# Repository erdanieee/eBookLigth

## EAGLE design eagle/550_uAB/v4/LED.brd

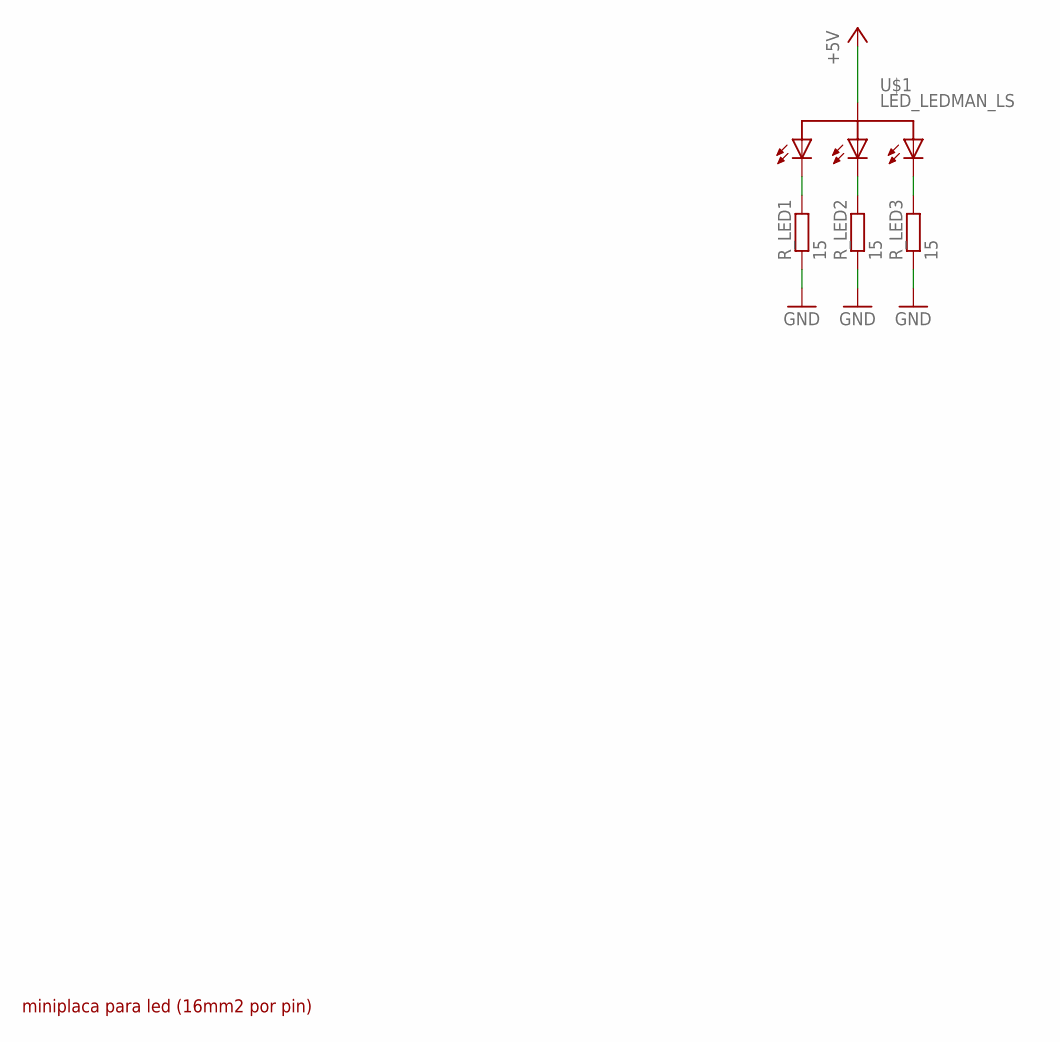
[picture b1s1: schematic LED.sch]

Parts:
R_LED1, R_LED2, R_LED3: 15; R1206
U$1: LED_LEDMAN_LS

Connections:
+5V: U$1.2 (ANODO)
GND: R_LED1.1, R_LED2.1, R_LED3.1
unnamed: R_LED1.2, U$1.1 (C1)
unnamed: R_LED2.2, U$1.3 (C2)
unnamed: R_LED3.2, U$1.4 (C3)

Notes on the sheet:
miniplaca para led (16mm2 por pin)

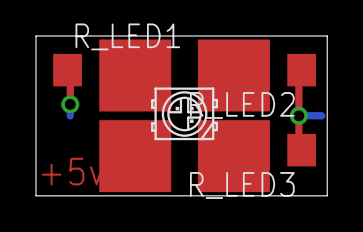
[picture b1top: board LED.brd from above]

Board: 2 copper layers, 16.2 x 8.9 mm, 4 parts (0 on the bottom side), 4 nets.

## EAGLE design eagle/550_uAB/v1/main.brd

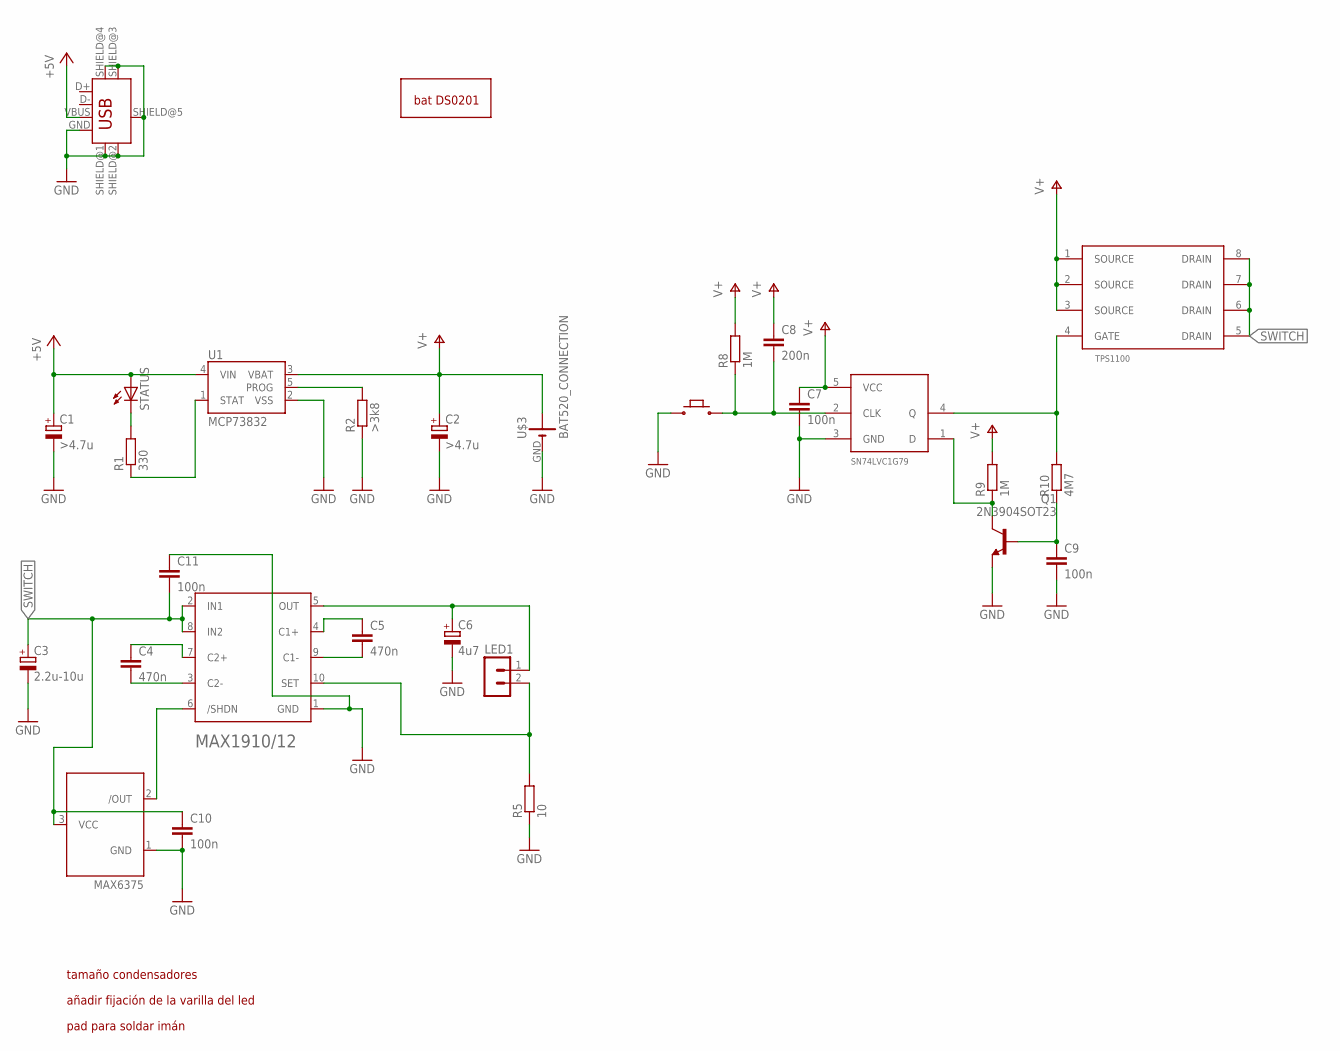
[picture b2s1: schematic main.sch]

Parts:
C1, C2: >4.7u; SMC_B
C3: 2.2u-10u; SMC_B
C4, C5: 470n; C1206
C6: 4u7; SMC_B
C7, C9, C10, C11: 100n; C1206
C8: 200n; C1206
LED1: MA02-1; MA02-1W
Q1: 2N3904SOT23; SOT23
R1: 330; R1206
R2: >3k8; R1206
R5: 10; R1206
R8, R9: 1M; R0805
R10: 4M7; R1206
STATUS: LEDCHIPLED_1206; CHIPLED_1206
U1: MCP73832; SOT23-5
U$1: MAX1910/12; UMAX/USOP_10L
U$2: MAX6375; SC70-3-W
U$3: BAT520_CONNECTION; BAT520_CONN_SMD
U$4: BAT_DS0201_PACKAGE; BAT_DS0201
U$5: MICROUSB_B; USB-MICROB
U$6: MICROBUTTON_0072; MICROBUTTON
U$7: SN74LVC1G79; SOT23-5
U$8: TPS1100; SO08

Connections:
+5V: C1.+, STATUS.A, U1.4 (VIN), U$5.VBUS
GND: C1.-, C2.-, C3.-, C6.-, C7.2, C9.2, C10.2, C11.1, Q1.2 (E), R2.1, R5.1, U1.2 (VSS), U$1.1 (GND), U$2.1 (GND), U$3.GND (-), U$5.GND, U$5.SHIELD@1 (SHIELD), U$5.SHIELD@2 (SHIELD), U$5.SHIELD@3 (SHIELD), U$5.SHIELD@4 (SHIELD), U$5.SHIELD@5 (SHIELD), U$6.P$2, U$7.3 (GND)
unnamed: Q1.3 (C), R9.1, U$7.1 (D)
unnamed: R1.2, STATUS.C
unnamed: R2.2, U1.5 (PROG)
unnamed: R1.1, U1.1 (STAT)
unnamed: C4.2, U$1.3 (C2-)
unnamed: C4.1, U$1.7 (C2+)
unnamed: C5.2, U$1.9 (C1-)
unnamed: C5.1, U$1.4 (C1+)
unnamed: LED1.2, R5.2, U$1.10 (SET)
unnamed: C6.+, LED1.1, U$1.5 (OUT)
unnamed: U$1.6 (/SHDN), U$2.2 (/OUT)
unnamed: C8.2, R8.1, U$6.P$1, U$7.2 (CLK)
unnamed: C9.1, Q1.1 (B), R10.1
unnamed: R10.2, U$7.4 (Q), U$8.4 (GATE)
SWITCH: C3.+, C10.1, C11.2, U$1.2 (IN1), U$1.8 (IN2), U$2.3 (VCC), U$8.5 (DRAIN), U$8.6 (DRAIN), U$8.7 (DRAIN), U$8.8 (DRAIN)
V+: C2.+, C7.1, C8.1, R8.2, R9.2, U1.3 (VBAT), U$3.VCC (+), U$7.5 (VCC), U$8.1 (SOURCE), U$8.2 (SOURCE), U$8.3 (SOURCE)

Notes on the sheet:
tamaño condensadores
añadir fijación de la varilla del led
pad para soldar imán

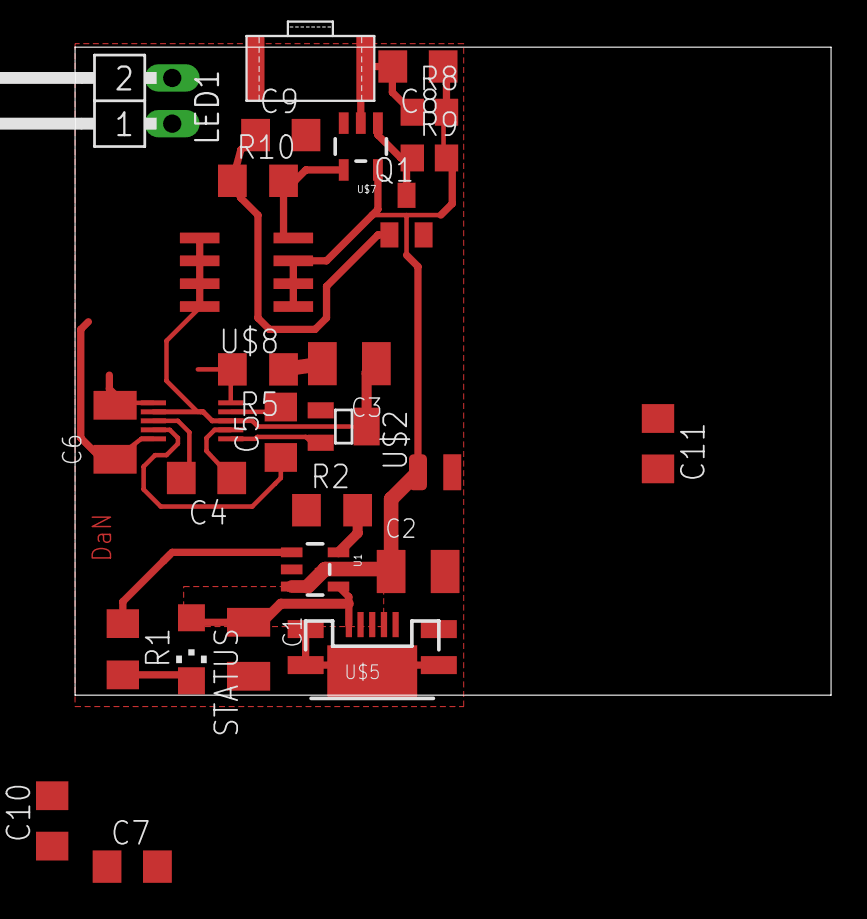
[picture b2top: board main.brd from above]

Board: 2 copper layers, 42.0 x 36.0 mm, 29 parts (0 on the bottom side), 18 nets.

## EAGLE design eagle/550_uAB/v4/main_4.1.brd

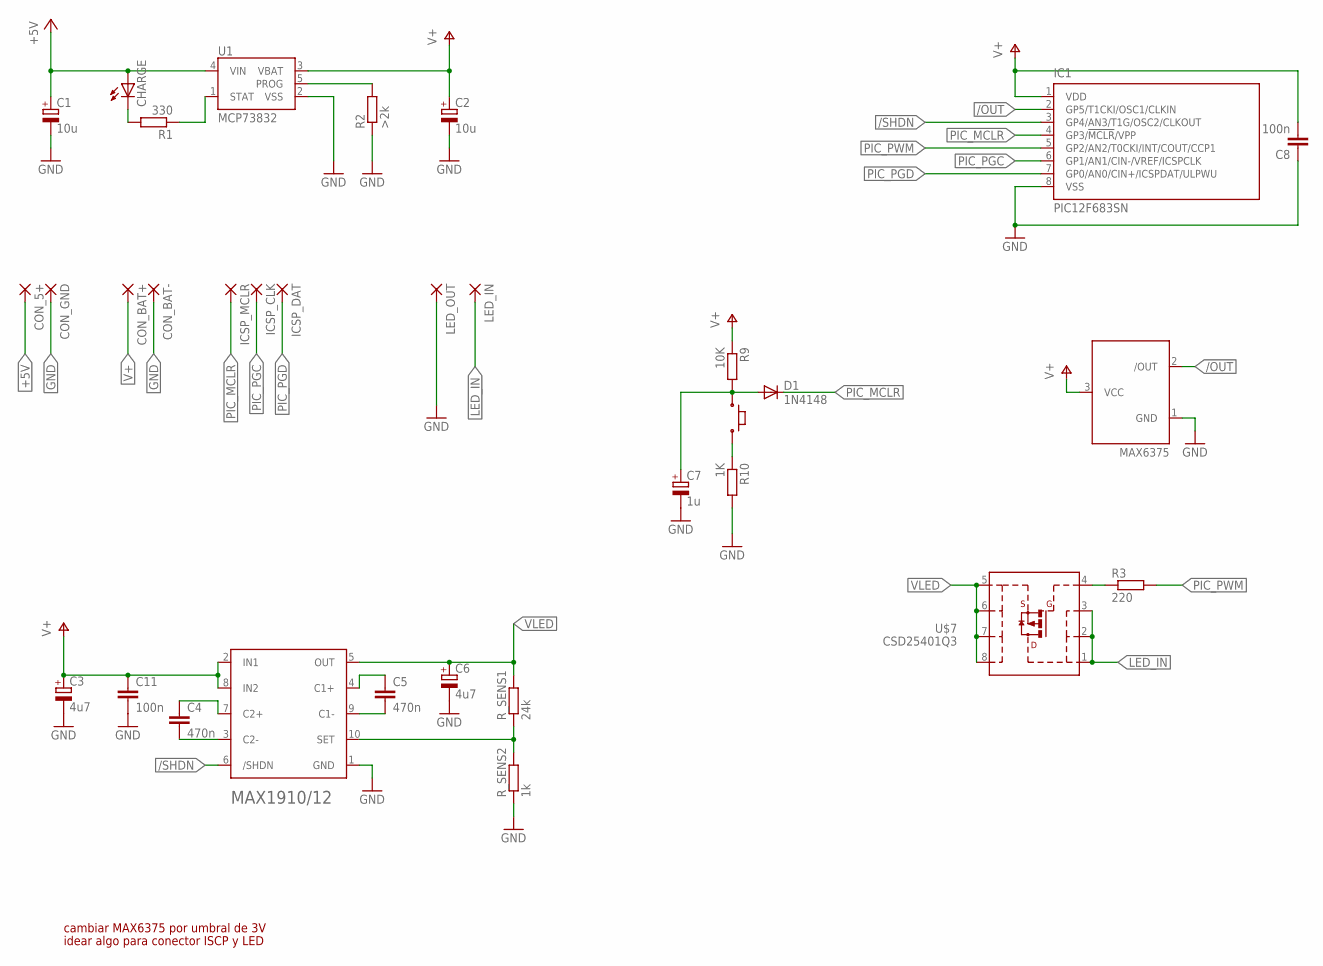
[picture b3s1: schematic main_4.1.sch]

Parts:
C1, C2: 10u; SMC_A
C3, C6: 4u7; SMC_A
C4, C5: 470n; C1206
C7: 1u; SMC_A
C8, C11: 100n; C1206
CHARGE: LEDCHIPLED_1206; CHIPLED_1206
CON_5+: SMD5; SMD2,54-5,08
CON_BAT+: SMD5; SMD2,54-5,08
CON_BAT-: SMD5; SMD2,54-5,08
CON_GND: SMD5; SMD2,54-5,08
D1: 1N4148; SOD80
IC1: PIC12F683SN; SO-08
ICSP_CLK: SMD5; SMD2,54-5,08
ICSP_DAT: SMD5; SMD2,54-5,08
ICSP_MCLR: SMD5; SMD2,54-5,08
LED_IN: SMD5; SMD2,54-5,08
LED_OUT: SMD5; SMD2,54-5,08
R1: 330; R1206
R2: >2k; R1206
R3: 220; R1206
R9: 10K; R1206
R10: 1K; R1206
R_SENS1: 24k; R1206
R_SENS2: 1k; R1206
U1: MCP73832; SOT23-5
U$1: MAX1910/12; UMAX/USOP_10L
U$2: MAX6375; SC70-3-W
U$6: MICROBUTTONE-MERCHAN; MICROBUTTON_2
U$7: CSD25401Q3; SON3X3

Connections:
+5V: C1.+, CHARGE.A, CON_5+.1, U1.4 (VIN)
/OUT: IC1.2 (GP5/T1CKI/OSC1/CLKIN), U$2.2 (/OUT)
/SHDN: IC1.3 (GP4/AN3/T1G/OSC2/CLKOUT), U$1.6 (/SHDN)
BUT: C7.+, D1.1 (A), R9.2, U$6.P$1
GND: C1.-, C2.-, C3.-, C6.-, C7.-, C8.1, C11.2, CON_BAT-.1, CON_GND.1, IC1.8 (VSS), LED_OUT.1, R2.1, R10.2, R_SENS2.1, U1.2 (VSS), U$1.1 (GND), U$2.1 (GND)
LED_IN: LED_IN.1, U$7.1, U$7.2, U$7.3
unnamed: R_SENS1.1, R_SENS2.2, U$1.10 (SET)
unnamed: R2.2, U1.5 (PROG)
unnamed: R1.1, U1.1 (STAT)
unnamed: C4.2, U$1.3 (C2-)
unnamed: C4.1, U$1.7 (C2+)
unnamed: C5.2, U$1.9 (C1-)
unnamed: C5.1, U$1.4 (C1+)
unnamed: R10.1, U$6.P$2
unnamed: R3.1, U$7.4
unnamed: CHARGE.C, R1.2
PIC_MCLR: D1.2 (C), IC1.4 (GP3/!MCLR!/VPP), ICSP_MCLR.1
PIC_PGC: IC1.6 (GP1/AN1/CIN-/VREF/ICSPCLK), ICSP_CLK.1
PIC_PGD: IC1.7 (GP0/AN0/CIN+/ICSPDAT/ULPWU), ICSP_DAT.1
PIC_PWM: IC1.5 (GP2/AN2/T0CKI/INT/COUT/CCP1), R3.2
V+: C2.+, C3.+, C8.2, C11.1, CON_BAT+.1, IC1.1 (VDD), R9.1, U1.3 (VBAT), U$1.2 (IN1), U$1.8 (IN2), U$2.3 (VCC)
VLED: C6.+, R_SENS1.2, U$1.5 (OUT), U$7.5, U$7.6, U$7.7, U$7.8

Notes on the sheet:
cambiar MAX6375 por umbral de 3V
idear algo para conector ISCP y LED

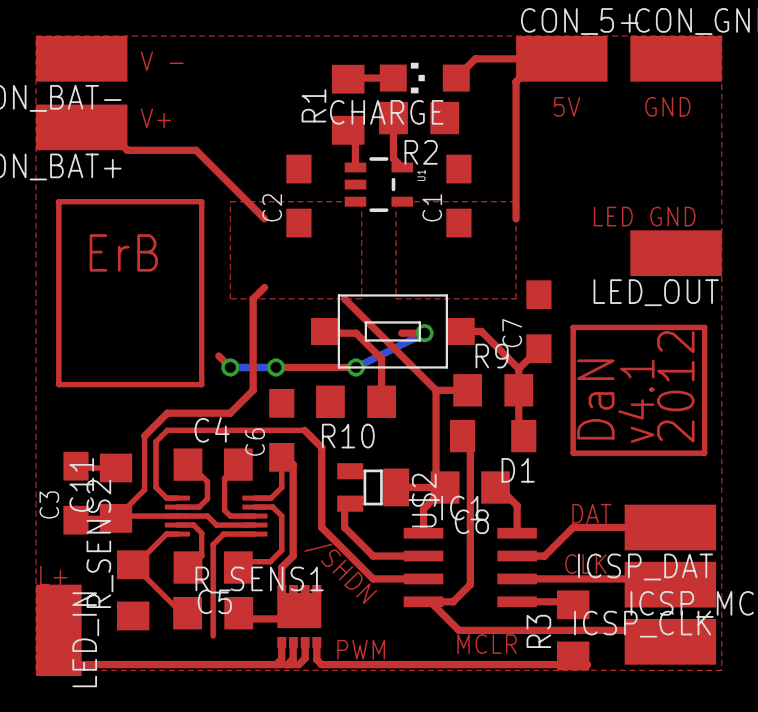
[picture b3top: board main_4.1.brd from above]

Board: 2 copper layers, 33 parts (0 on the bottom side), 22 nets.

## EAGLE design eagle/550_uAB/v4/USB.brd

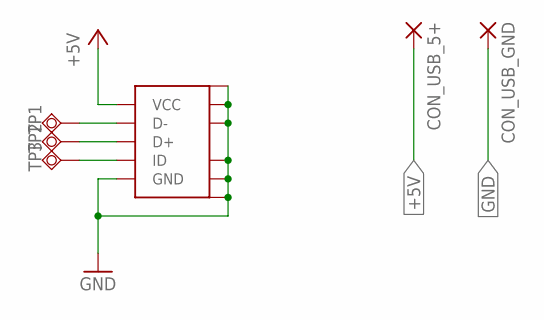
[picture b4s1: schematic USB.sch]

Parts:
CON_USB_5+: SMD5; SMD2,54-5,08
CON_USB_GND: SMD5; SMD2,54-5,08
TP1, TP2, TP3: TPSQB1,27; B1,27
U$5: MICRO_USB_B

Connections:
+5V: CON_USB_5+.1, U$5.1 (VCC)
GND: CON_USB_GND.1, U$5.5 (GND), U$5.GND1 (GND), U$5.GND2 (GND), U$5.GND3 (GND), U$5.GND4 (GND), U$5.GND5 (GND), U$5.GND6 (GND)
unnamed: TP1.TP, U$5.2 (D-)
unnamed: TP2.TP, U$5.3 (D+)
unnamed: TP3.TP, U$5.4 (ID)

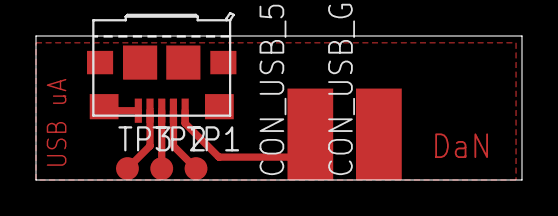
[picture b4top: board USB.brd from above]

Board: 2 copper layers, 27.0 x 8.0 mm, 6 parts (0 on the bottom side), 5 nets.

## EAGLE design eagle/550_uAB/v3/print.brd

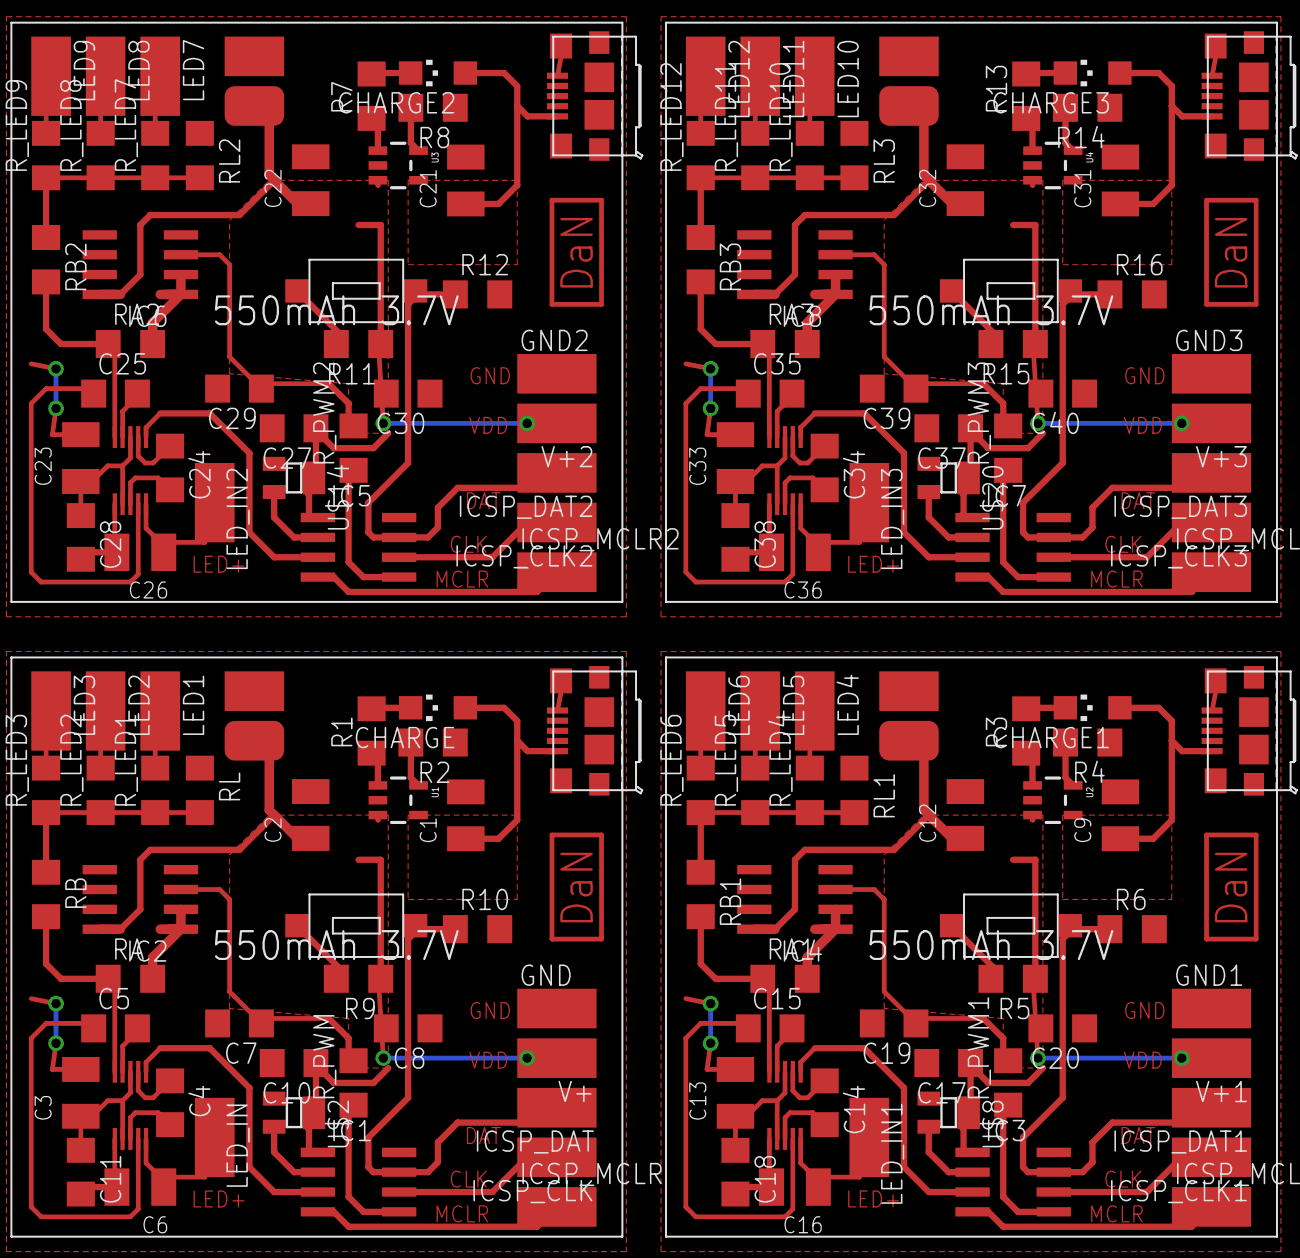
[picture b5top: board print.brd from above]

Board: 2 copper layers, 160 parts (0 on the bottom side), 104 nets.

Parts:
C1, C2, C9, C12, C21, C22, C31, C32: >4.7u; SMC_B
C3, C13, C23, C33: 2.2u-10u; SMC_B
C4, C5, C7, C14, C15, C19, C24, C25, C29, C34, C35, C39: 470n; C1206
C6, C16, C26, C36: 4u7; SMC_B
C8, C10, C11, C17, C18, C20, C27, C28, C30, C37, C38, C40: 100n; C1206
CHARGE, CHARGE1, CHARGE2, CHARGE3: CHIPLED_1206
GND, GND1, GND2, GND3: SMD2,54-5,08
IC1, IC3, IC5, IC7: PIC12F683SN; SO-08
IC2, IC4, IC6, IC8: LM358D; SO08
ICSP_CLK, ICSP_CLK1, ICSP_CLK2, ICSP_CLK3: SMD2,54-5,08
ICSP_DAT, ICSP_DAT1, ICSP_DAT2, ICSP_DAT3: SMD2,54-5,08
ICSP_MCLR, ICSP_MCLR1, ICSP_MCLR2, ICSP_MCLR3: SMD2,54-5,08
LED1, LED2, LED3, LED4, LED5, LED6, LED7, LED8, LED9, LED10, LED11, LED12: SMD2,54-5,08
LED_IN, LED_IN1, LED_IN2, LED_IN3: SMD2,54-5,08
R1, R3, R7, R13: 330; R1206
R2, R4, R8, R14: >3k8; R1206
R5, R9, R11, R15: 1K; R1206
R6, R10, R12, R16: 10K; R1206
RA, RA1, RA2, RA3: R1206
RB, RB1, RB2, RB3: R1206
RL, RL1, RL2, RL3: R1206
R_LED1, R_LED2, R_LED3, R_LED4, R_LED5, R_LED6, R_LED7, R_LED8, R_LED9, R_LED10, R_LED11, R_LED12: R1206
R_PWM, R_PWM1, R_PWM2, R_PWM3: R1206
U1, U2, U3, U4: MCP73832; SOT23-5
U$1, U$7, U$13, U$19: MAX1910/12; UMAX/USOP_10L
U$2, U$8, U$14, U$20: MAX6375; SC70-3-W
U$3, U$9, U$15, U$21: BAT520_CONNECTION; BAT520_CONN_SMD
U$4, U$10, U$16, U$22: BAT_DS0201_PACKAGE; BAT_DS0201
U$5, U$11, U$17, U$23: MICRO_USB_B
U$6, U$12, U$18, U$24: MICROBUTTONE-MERCHAN; MICROBUTTON_2
V+, V+1, V+2, V+3: SMD2,54-5,08

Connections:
+5V: C1.+, CHARGE.A, U1.4, U$5.1
+5V1: C9.+, CHARGE1.A, U2.4, U$11.1
+5V2: C21.+, CHARGE2.A, U3.4, U$17.1
+5V3: C31.+, CHARGE3.A, U4.4, U$23.1
/OUT: IC1.2, U$2.2
/OUT1: IC3.2, U$8.2
/OUT2: IC5.2, U$14.2
/OUT3: IC7.2, U$20.2
/SHDN: IC1.3, U$1.6
/SHDN1: IC3.3, U$7.6
/SHDN2: IC5.3, U$13.6
/SHDN3: IC7.3, U$19.6
GND: C1.-, C2.-, C3.-, C6.-, C7.2, C8.1, C10.2, C11.2, GND.1, IC1.8, IC2.4, R2.1, R10.2, RL.1, U1.2, U$1.1, U$2.1, U$3.GND, U$5.5, U$5.GND1, U$5.GND2, U$5.GND3, U$5.GND4, U$5.GND5, U$5.GND6
GND1: C9.-, C12.-, C13.-, C16.-, C17.2, C18.2, C19.2, C20.1, GND1.1, IC3.8, IC4.4, R4.1, R6.2, RL1.1, U2.2, U$7.1, U$8.1, U$9.GND, U$11.5, U$11.GND1, U$11.GND2, U$11.GND3, U$11.GND4, U$11.GND5, U$11.GND6
GND2: C21.-, C22.-, C23.-, C26.-, C27.2, C28.2, C29.2, C30.1, GND2.1, IC5.8, IC6.4, R8.1, R12.2, RL2.1, U3.2, U$13.1, U$14.1, U$15.GND, U$17.5, U$17.GND1, U$17.GND2, U$17.GND3, U$17.GND4, U$17.GND5, U$17.GND6
GND3: C31.-, C32.-, C33.-, C36.-, C37.2, C38.2, C39.2, C40.1, GND3.1, IC7.8, IC8.4, R14.1, R16.2, RL3.1, U4.2, U$19.1, U$20.1, U$21.GND, U$23.5, U$23.GND1, U$23.GND2, U$23.GND3, U$23.GND4, U$23.GND5, U$23.GND6
LED_DAC: IC2.1, IC2.2, RA.2
LED_DAC1: IC4.1, IC4.2, RA1.2
LED_DAC2: IC6.1, IC6.2, RA2.2
LED_DAC3: IC8.1, IC8.2, RA3.2
unnamed: RB.1, RL.2, R_LED1.1, R_LED2.1, R_LED3.1
unnamed: C7.1, IC2.3, R_PWM.2
unnamed: R2.2, U1.5
unnamed: R1.1, U1.1
unnamed: C4.2, U$1.3
unnamed: C4.1, U$1.7
unnamed: C5.2, U$1.9
unnamed: C5.1, U$1.4
unnamed: LED3.1, R_LED3.2
unnamed: LED2.1, R_LED2.2
unnamed: RA.1, RB.2, U$1.10
unnamed: LED1.1, R_LED1.2
unnamed: C6.+, LED_IN.1, U$1.5
unnamed: CHARGE.C, R1.2
unnamed: R9.2, U$6.P$1
unnamed: R4.2, U2.5
unnamed: C14.2, U$7.3
unnamed: C14.1, U$7.7
unnamed: C15.2, U$7.9
unnamed: C15.1, U$7.4
unnamed: RA1.1, RB1.2, U$7.10
unnamed: C16.+, LED_IN1.1, U$7.5
unnamed: RB1.1, RL1.2, R_LED4.1, R_LED5.1, R_LED6.1
unnamed: LED6.1, R_LED6.2
unnamed: LED5.1, R_LED5.2
unnamed: LED4.1, R_LED4.2
unnamed: CHARGE1.C, R3.2
unnamed: R3.1, U2.1
unnamed: C19.1, IC4.3, R_PWM1.2
unnamed: R5.2, U$12.P$1
unnamed: R8.2, U3.5
unnamed: C24.2, U$13.3
unnamed: C24.1, U$13.7
unnamed: C25.2, U$13.9
unnamed: C25.1, U$13.4
unnamed: RA2.1, RB2.2, U$13.10
unnamed: C26.+, LED_IN2.1, U$13.5
unnamed: RB2.1, RL2.2, R_LED7.1, R_LED8.1, R_LED9.1
unnamed: LED9.1, R_LED9.2
unnamed: LED8.1, R_LED8.2
unnamed: LED7.1, R_LED7.2
unnamed: CHARGE2.C, R7.2
unnamed: R7.1, U3.1
unnamed: C29.1, IC6.3, R_PWM2.2
unnamed: R11.2, U$18.P$1
unnamed: R14.2, U4.5
unnamed: C34.2, U$19.3
unnamed: C34.1, U$19.7
unnamed: C35.2, U$19.9
unnamed: C35.1, U$19.4
unnamed: RA3.1, RB3.2, U$19.10
unnamed: C36.+, LED_IN3.1, U$19.5
unnamed: RB3.1, RL3.2, R_LED10.1, R_LED11.1, R_LED12.1
unnamed: LED12.1, R_LED12.2
unnamed: LED11.1, R_LED11.2
unnamed: LED10.1, R_LED10.2
unnamed: CHARGE3.C, R13.2
unnamed: R13.1, U4.1
unnamed: C39.1, IC8.3, R_PWM3.2
unnamed: R15.2, U$24.P$1
PIC_MCLR: IC1.4, ICSP_MCLR.1
PIC_MCLR1: IC3.4, ICSP_MCLR1.1
PIC_MCLR2: IC5.4, ICSP_MCLR2.1
PIC_MCLR3: IC7.4, ICSP_MCLR3.1
PIC_PGC: IC1.6, ICSP_CLK.1
PIC_PGC1: IC3.6, ICSP_CLK1.1
PIC_PGC2: IC5.6, ICSP_CLK2.1
PIC_PGC3: IC7.6, ICSP_CLK3.1
PIC_PGD: IC1.7, ICSP_DAT.1, R10.1, U$6.P$2
PIC_PGD1: IC3.7, ICSP_DAT1.1, R6.1, U$12.P$2
PIC_PGD2: IC5.7, ICSP_DAT2.1, R12.1, U$18.P$2
PIC_PGD3: IC7.7, ICSP_DAT3.1, R16.1, U$24.P$2
PIC_PWM: IC1.5, R_PWM.1
PIC_PWM1: IC3.5, R_PWM1.1
PIC_PWM2: IC5.5, R_PWM2.1
PIC_PWM3: IC7.5, R_PWM3.1
SWITCH: C3.+, C11.1, U$1.2, U$1.8
SWITCH1: C13.+, C18.1, U$7.2, U$7.8
SWITCH2: C23.+, C28.1, U$13.2, U$13.8
SWITCH3: C33.+, C38.1, U$19.2, U$19.8
V+: C2.+, C8.2, C10.1, IC1.1, IC2.8, R9.1, U1.3, U$2.3, U$3.VCC, V+.1
V+1: C12.+, C17.1, C20.2, IC3.1, IC4.8, R5.1, U2.3, U$8.3, U$9.VCC, V+1.1
V+2: C22.+, C27.1, C30.2, IC5.1, IC6.8, R11.1, U3.3, U$14.3, U$15.VCC, V+2.1
V+3: C32.+, C37.1, C40.2, IC7.1, IC8.8, R15.1, U4.3, U$20.3, U$21.VCC, V+3.1

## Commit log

2016-09-07 eagle files
